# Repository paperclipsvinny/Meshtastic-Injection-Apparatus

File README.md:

# Mesh Injection Apparatus (M.I.A.) 
A tool that combines HID injection with LoRa (Meshtastic) mesh networking for a red team implant that doesn't rely on WiFi or internet for C2. 

## DISCLAIMER: 
**This is a covert keystroke injection tool, designed for Red Teams, Penetration Testers, and authorized testing only. Do NOT use this tool on any systems which you have not been given express, explicit permission. I, the author, am not responsible for any damages which may incur from using this tool.** 

## Where is everything?
For Firmware Architecture notes, check out [ARCHITECTURE.md](./ARCHITECTURE.md). 
Hardware, Schematics and PCB manufacturing files can be found under [`/Hardware`](./Hardware) . 

For technical Documentation, head over to [DOCUMENTATION.md](docs/DOCUMENTATION.md), also available at [TheMIA.dev](https://themia.dev)

As debuted at the [DEF CON 34 Main stage](https://defcon.org/html/defcon-34/dc-34-speakers.html#content_66655)

## LICENSE: 
This project is released under the **MIT license**. 
 Anyone is permitted to modify, distribute, and use anything from this project for both private and commercial use. 
### Conditions: 
You must provide a copy of the original copyright notice and include the full MIT license text, found in LICENSE.txt. 
### Limitations: 
The software is NOT under any warranty, and the author will not be held responsible for any damages or issues arising from this software. The original Author’s name and original logos cannot be used for marketing or promotion. 

## Credits & Inspiration
- **[Meshtastic](https://meshtastic.org)** — the mesh protocol MIA builds on
- **[RadioLib](https://github.com/jgromes/RadioLib)** — LoRa radio abstraction
- **[Loki](https://github.com/RocketGod-git/Meshtastic-Loki)** — Meshtastic fork that added HID 
  support, the direct inspiration for MIA's development. 
- **[EvilCrowRF](https://github.com/joelsernamoreno/EvilCrowRF-V2)** — web dashboard 
  design inspiration.

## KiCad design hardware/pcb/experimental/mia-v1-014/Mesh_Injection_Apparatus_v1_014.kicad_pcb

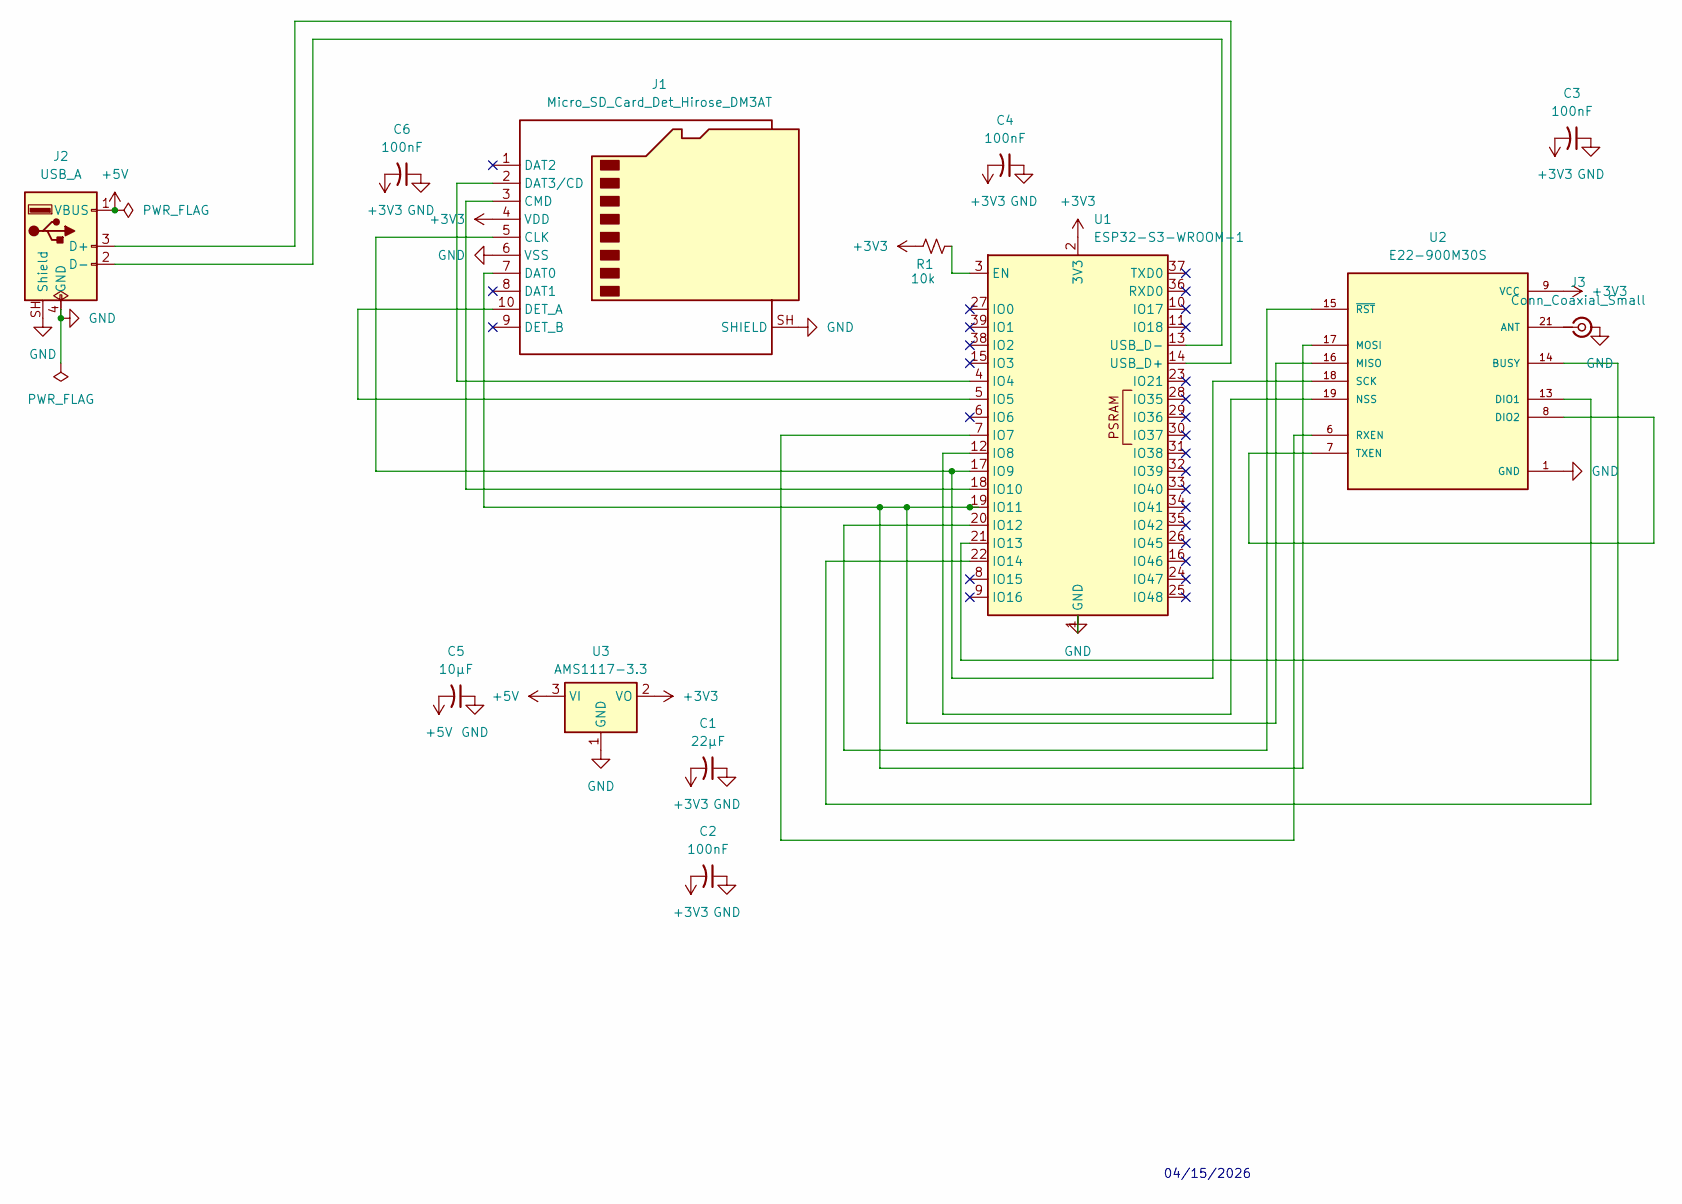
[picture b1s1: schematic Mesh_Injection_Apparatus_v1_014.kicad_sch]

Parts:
C1: 22μF; C_0805_2012Metric
C2, C3, C4, C6: 100nF; C_0805_2012Metric
C5: 10μF; C_0805_2012Metric
J1: Micro_SD_Card_Det_Hirose_DM3AT
J2: USB_A; USB3_A_Plug_Wuerth_692112030100_Horizontal
J3: Conn_Coaxial_Small; U.FL_Hirose_U.FL-R-SMT-1_Vertical
R1: 10k; R_0805_2012Metric_Pad1.20x1.40mm_HandSolder
U1: ESP32-S3-WROOM-1
U2: E22-900M30S; XCVR_E22-900M30S; PARTREV 1.2
U3: AMS1117-3.3; SOT-223-3_TabPin2

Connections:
+3V3: C1.2, C2.2, C3.2, C4.2, C6.2, J1.4 (VDD), R1.1, U1.2 (3V3), U2.9 (VCC), U2.10 (VCC), U3.2 (VO)
+5V: C5.2, J2.1 (VBUS), U3.3 (VI)
GND: C1.1, C2.1, C3.1, C4.1, C5.1, C6.1, J1.6 (VSS), J1.SH (SHIELD), J2.4 (GND), J2.SH (Shield), J3.2 (Ext), U1.1 (GND), U1.40 (GND), U1.41 (GND), U2.1 (GND), U2.2 (GND), U2.3 (GND), U2.4 (GND), U2.5 (GND), U2.11 (GND), U2.12 (GND), U2.20 (GND), U2.22 (GND), U3.1 (GND)
unnamed: J1.5 (CLK), U1.17 (IO9), U2.18 (SCK)
unnamed: J1.3 (CMD), U1.18 (IO10)
unnamed: J1.7 (DAT0), U1.19 (IO11), U2.16 (MISO), U2.17 (MOSI)
unnamed: J1.2 (DAT3/CD), U1.4 (IO4)
unnamed: J1.10 (DET_A), U1.5 (IO5)
unnamed: J2.3 (D+), U1.14 (USB_D+)
unnamed: J2.2 (D-), U1.13 (USB_D-)
unnamed: J3.1 (In), U2.21 (ANT)
unnamed: R1.2, U1.3 (EN)
unnamed: U1.7 (IO7), U2.6 (RXEN)
unnamed: U1.12 (IO8), U2.19 (NSS)
unnamed: U1.20 (IO12), U2.15 (~RST)
unnamed: U1.21 (IO13), U2.14 (BUSY)
unnamed: U1.22 (IO14), U2.13 (DIO1)
unnamed: U2.7 (TXEN), U2.8 (DIO2)

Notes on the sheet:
04/15/2026

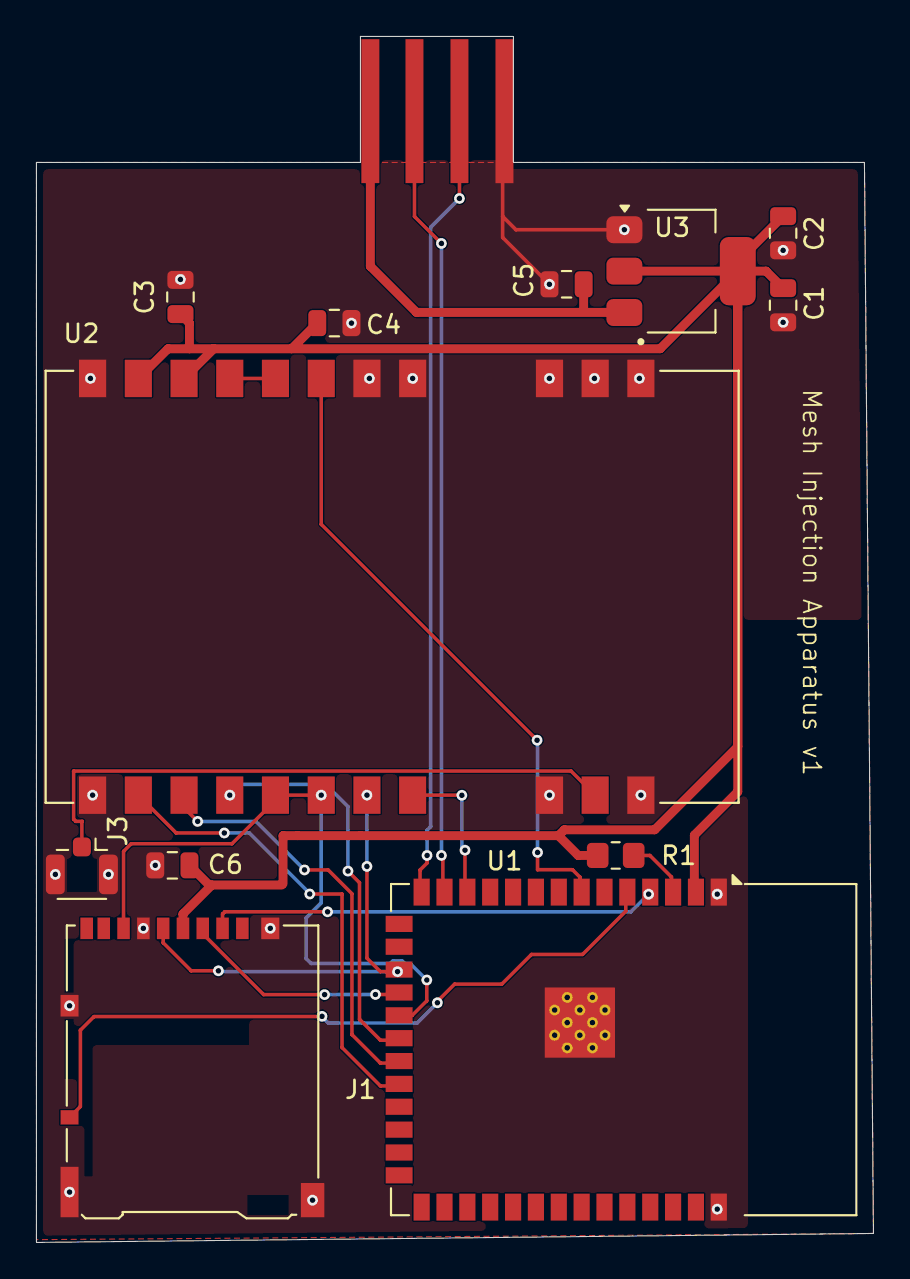
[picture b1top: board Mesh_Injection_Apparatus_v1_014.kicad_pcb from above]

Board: 2 copper layers, 46.5 x 67.0 mm, 12 parts (0 on the bottom side), 16 nets.

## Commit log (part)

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2026-04-16 working DuckyScript Parser
